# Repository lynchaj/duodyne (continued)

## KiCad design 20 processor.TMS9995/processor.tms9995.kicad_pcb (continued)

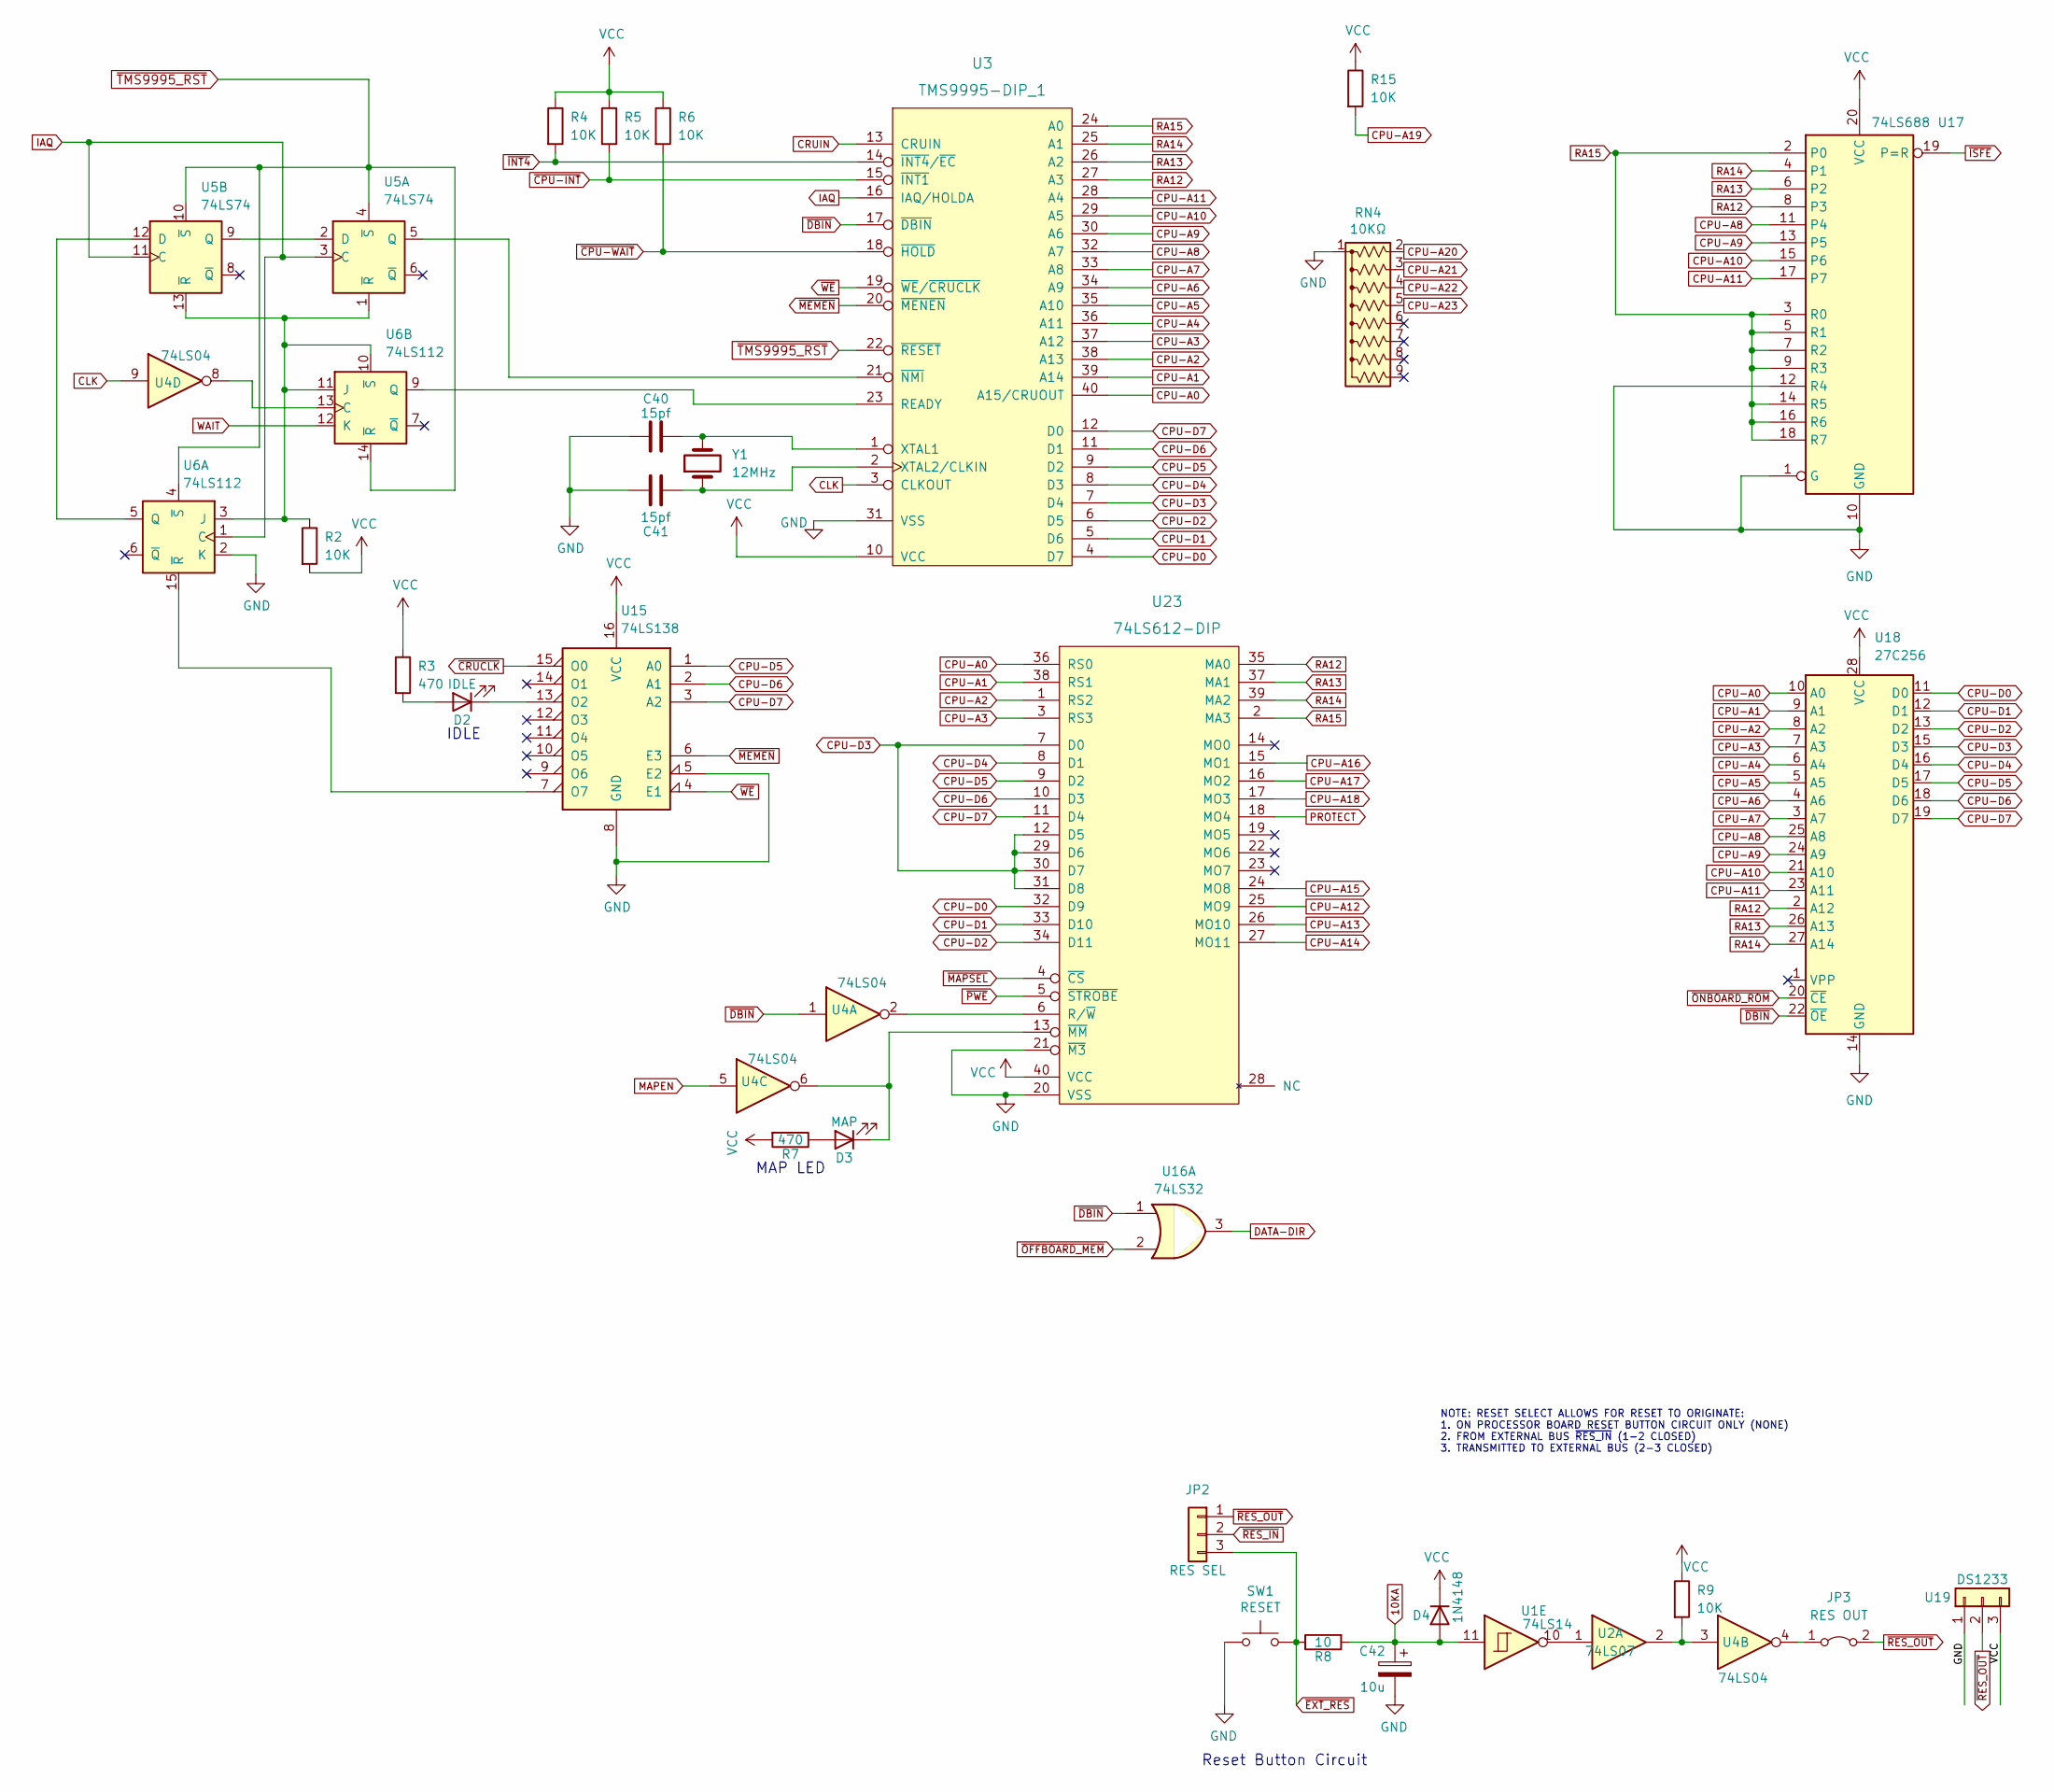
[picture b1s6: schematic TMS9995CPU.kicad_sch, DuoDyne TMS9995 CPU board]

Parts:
C40, C41: 15pf; C_Disc_D5.0mm_W2.5mm_P5.00mm
C42: 10u; CP_Radial_D5.0mm_P2.50mm
D2: IDLE; LED_D3.0mm_Horizontal_O3.81mm_Z2.0mm
D3: MAP; LED_D3.0mm_Horizontal_O3.81mm_Z2.0mm
D4: 1N4148; D_DO-35_SOD27_P7.62mm_Horizontal
JP2: RES SEL; PinHeader_1x03_P2.54mm_Vertical
JP3: RES OUT; SolderJumper-2_P1.3mm_Bridged_Pad1.0x1.5mm
R2, R4, R5, R6, R9, R15: 10K; R_Axial_DIN0207_L6.3mm_D2.5mm_P7.62mm_Horizontal
R3, R7: 470; R_Axial_DIN0207_L6.3mm_D2.5mm_P7.62mm_Horizontal
R8: 10; R_Axial_DIN0207_L6.3mm_D2.5mm_P7.62mm_Horizontal
RN4: 10KΩ; R_Array_SIP9
SW1: RESET; SW_Tactile_SPST_Angled_PTS645Vx58-2LFS
U1: 74LS14; DIP-14_W7.62mm_Socket_LongPads
U2: 74LS07; DIP-14_W7.62mm_Socket_LongPads
U3: TMS9995-DIP_1; DIP-40_W15.24mm_Socket_LongPads
U4: 74LS04; DIP-14_W7.62mm_Socket_LongPads
U5: 74LS74; DIP-14_W7.62mm_Socket_LongPads
U6: 74LS112; DIP-16_W7.62mm_Socket_LongPads
U15: 74LS138; DIP-16_W7.62mm_Socket_LongPads
U16: 74LS32; DIP-14_W7.62mm_Socket_LongPads
U17: 74LS688; DIP-20_W7.62mm_Socket_LongPads
U18: 27C256; DIP-28_W15.24mm_Socket_LongPads
U19: DS1233; TO-92L_HandSolder
U23: 74LS612-DIP; DIP-40_W15.24mm_Socket_LongPads
Y1: 12MHz; Crystal_HC49-U_Vertical

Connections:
10KA: C42.1, D4.2 (A), R8.2, U1.11
CLK: U3.3 (CLKOUT), U4.9; also elsewhere on the board
CPU-A0: U3.40 (A15/CRUOUT), U18.10 (A0), U23.36 (RS0); also elsewhere on the board
CPU-A1: U3.39 (A14), U18.9 (A1), U23.38 (RS1); also elsewhere on the board
CPU-A2: U3.38 (A13), U18.8 (A2), U23.1 (RS2); also elsewhere on the board
CPU-A3: U3.37 (A12), U18.7 (A3), U23.3 (RS3); also elsewhere on the board
CPU-A4: U3.36 (A11), U18.6 (A4); also elsewhere on the board
CPU-A5: U3.35 (A10), U18.5 (A5); also elsewhere on the board
CPU-A6: U3.34 (A9), U18.4 (A6); also elsewhere on the board
CPU-A7: U3.33 (A8), U18.3 (A7); also elsewhere on the board
CPU-A8: U3.32 (A7), U17.11 (P4), U18.25 (A8); also elsewhere on the board
CPU-A9: U3.30 (A6), U17.13 (P5), U18.24 (A9); also elsewhere on the board
CPU-A10: U3.29 (A5), U17.15 (P6), U18.21 (A10); also elsewhere on the board
CPU-A11: U3.28 (A4), U17.17 (P7), U18.23 (A11); also elsewhere on the board
CPU-A12: U23.25 (MO9); also elsewhere on the board
CPU-A13: U23.26 (MO10); also elsewhere on the board
CPU-A14: U23.27 (MO11); also elsewhere on the board
CPU-A15: U23.24 (MO8); also elsewhere on the board
CPU-A16: U23.15 (MO1); also elsewhere on the board
CPU-A17: U23.16 (MO2); also elsewhere on the board
CPU-A18: U23.17 (MO3); also elsewhere on the board
CPU-A19: R15.2; also elsewhere on the board
CPU-A20: RN4.2 (R1); also elsewhere on the board
CPU-A21: RN4.3 (R2); also elsewhere on the board
CPU-A22: RN4.4 (R3); also elsewhere on the board
CPU-A23: RN4.5 (R4); also elsewhere on the board
CPU-D0: U3.4 (D7), U18.11 (D0), U23.32 (D9); also elsewhere on the board
CPU-D1: U3.5 (D6), U18.12 (D1), U23.33 (D10); also elsewhere on the board
CPU-D2: U3.6 (D5), U18.13 (D2), U23.34 (D11); also elsewhere on the board
CPU-D3: U3.7 (D4), U18.15 (D3), U23.7 (D0), U23.12 (D5), U23.29 (D6), U23.30 (D7), U23.31 (D8); also elsewhere on the board
CPU-D4: U3.8 (D3), U18.16 (D4), U23.8 (D1); also elsewhere on the board
CPU-D5: U3.9 (D2), U15.1 (A0), U18.17 (D5), U23.9 (D2); also elsewhere on the board
CPU-D6: U3.11 (D1), U15.2 (A1), U18.18 (D6), U23.10 (D3); also elsewhere on the board
CPU-D7: U3.12 (D0), U15.3 (A2), U18.19 (D7), U23.11 (D4); also elsewhere on the board
CRUIN: U3.13 (CRUIN); also elsewhere on the board
DATA-DIR: U16.3; also elsewhere on the board
GND: C40.1, C41.1, C42.2, RN4.1 (common), SW1.2, U3.31 (VSS), U6.2 (K), U15.5 (E2), U15.8 (GND), U17.1 (G), U17.10 (GND), U17.12 (R4), U18.14 (GND), U19.1, U23.20 (VSS), U23.21 (~M3); also elsewhere on the board
IAQ: U3.16 (IAQ/HOLDA), U5.3 (C), U5.11 (C), U6.1 (C)
MAPEN: U4.5; also elsewhere on the board
unnamed: C40.2, U3.1 (XTAL1), Y1.2
unnamed: C41.2, U3.2 (XTAL2/CLKIN), Y1.1
unnamed: D2.1 (K), U15.13 (O2)
unnamed: D2.2 (A), R3.2
unnamed: D3.1 (K), U4.6, U23.13 (~MM)
unnamed: D3.2 (A), R7.1
unnamed: JP3.1 (A), U4.4
unnamed: R2.1, U5.1 (~R), U5.13 (~R), U6.3 (J), U6.10 (~S), U6.11 (J)
unnamed: R9.2, U2.2, U4.3
unnamed: U1.10, U2.1
unnamed: U4.2, U23.6 (R/~W)
unnamed: U4.8, U6.13 (C)
unnamed: U5.2 (D), U5.9 (Q)
unnamed: U3.21 (~NMI), U5.5 (Q)
unnamed: U5.12 (D), U6.5 (Q)
unnamed: U3.23 (READY), U6.9 (Q)
unnamed: U6.15 (~R), U15.7 (O7)
PROTECT: U23.18 (MO4); also elsewhere on the board
RA12: U3.27 (A3), U17.8 (P3), U18.2 (A12), U23.35 (MA0)
RA13: U3.26 (A2), U17.6 (P2), U18.26 (A13), U23.37 (MA1)
RA14: U3.25 (A1), U17.4 (P1), U18.27 (A14), U23.39 (MA2)
RA15: U3.24 (A0), U17.2 (P0), U17.3 (R0), U17.5 (R1), U17.7 (R2), U17.9 (R3), U17.14 (R5), U17.16 (R6), U17.18 (R7), U23.2 (MA3); also elsewhere on the board
VCC: D4.1 (K), R2.2, R3.1, R4.1, R5.1, R6.1, R7.2, R9.1, R15.1, U3.10 (VCC), U15.16 (VCC), U17.20 (VCC), U18.28 (VCC), U19.3, U23.40 (VCC); also elsewhere on the board
WAIT: U6.12 (K); also elsewhere on the board
~CPU-INT: R5.2, U3.15 (~INT1); also elsewhere on the board
~CPU-WAIT: R6.2, U3.18 (~HOLD); also elsewhere on the board
~CRUCLK: U15.15 (O0); also elsewhere on the board
~DBIN: U3.17 (~DBIN), U4.1, U16.1, U18.22 (~OE); also elsewhere on the board
~EXT_RES: JP2.3, R8.1, SW1.1
~INT4: R4.2, U3.14 (~INT4/~EC); also elsewhere on the board
~ISFE: U17.19 (P=R); also elsewhere on the board
~MAPSEL: U23.4 (~CS); also elsewhere on the board
~MEMEN: U3.20 (~MENEN), U15.6 (E3); also elsewhere on the board
~OFFBOARD_MEM: U16.2; also elsewhere on the board
~ONBOARD_ROM: U18.20 (~CE); also elsewhere on the board
~PWE: U23.5 (~STROBE); also elsewhere on the board
~RES_IN: JP2.2; also elsewhere on the board
~RES_OUT: JP2.1, JP3.2 (B), U19.2; also elsewhere on the board
~TMS9995_RST: U3.22 (~RESET), U5.4 (~S), U5.10 (~S), U6.4 (~S), U6.14 (~R); also elsewhere on the board
~WE: U3.19 (~WE/~CRUCLK), U15.4 (E1); also elsewhere on the board

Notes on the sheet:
Reset Button Circuit
MAP LED
IDLE
NOTE: RESET SELECT ALLOWS FOR RESET TO ORIGINATE: 1. ON PROCESSOR BOARD RESET BUTTON CIRCUIT ONLY (NONE) 2. FROM EXTERNAL BUS ~{RES_IN} (1-2 CLOSED) 3. TRANSMITTED TO EXTERNAL BUS (2-3 CLOSED)

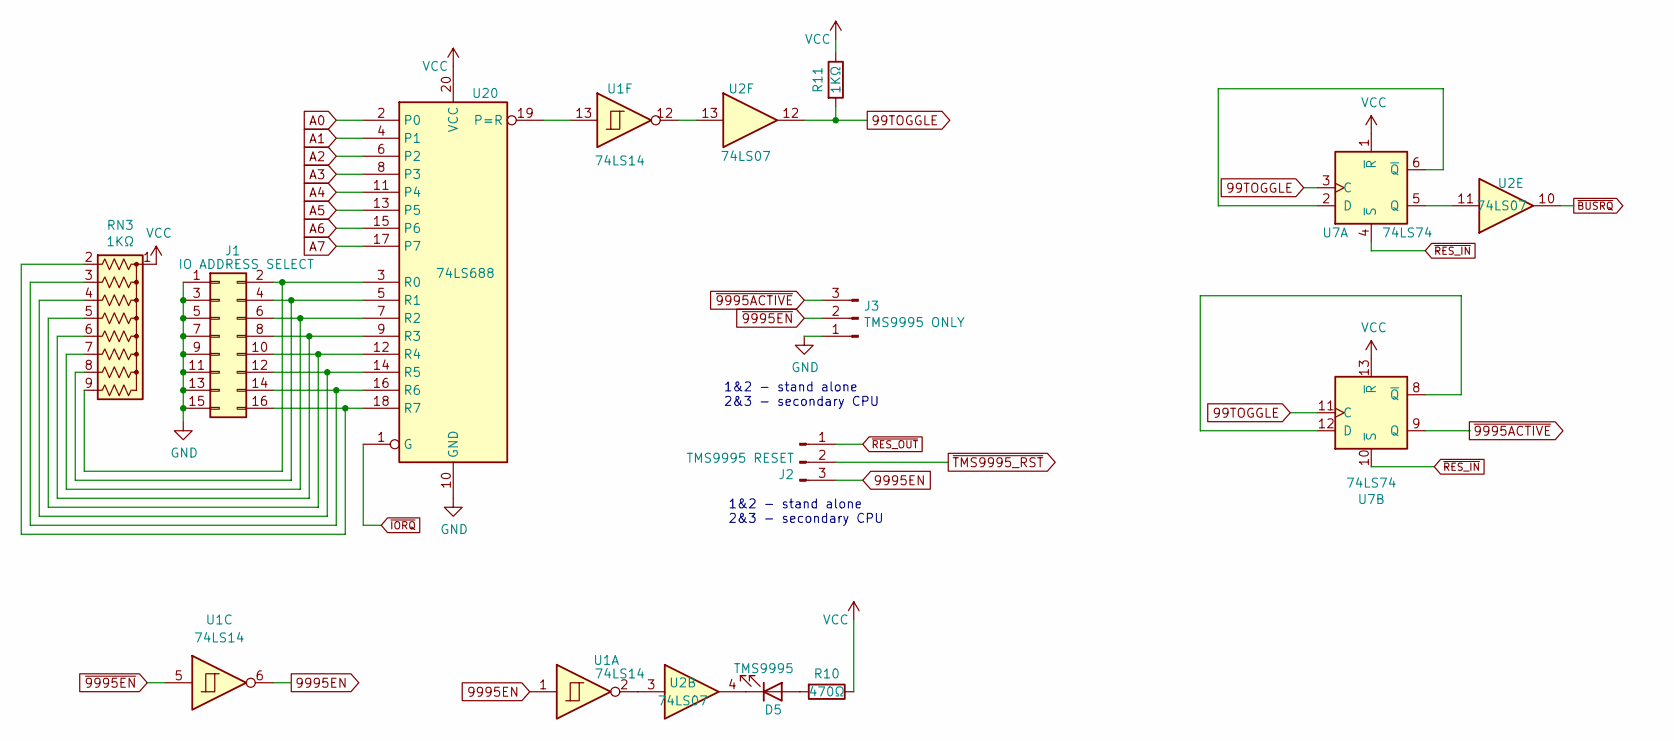
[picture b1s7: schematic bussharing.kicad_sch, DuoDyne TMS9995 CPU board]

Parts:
D5: TMS9995; LED_D3.0mm_Horizontal_O3.81mm_Z2.0mm
J1: IO ADDRESS SELECT; PinHeader_2x08_P2.54mm_Vertical
J2: TMS9995 RESET; PinHeader_1x03_P2.54mm_Horizontal
J3: TMS9995 ONLY; PinHeader_1x03_P2.54mm_Horizontal
R10: 470Ω; R_Axial_DIN0207_L6.3mm_D2.5mm_P7.62mm_Horizontal
R11: 1KΩ; R_Axial_DIN0207_L6.3mm_D2.5mm_P7.62mm_Horizontal
RN3: 1KΩ; R_Array_SIP9
U1: 74LS14; DIP-14_W7.62mm_Socket_LongPads
U2: 74LS07; DIP-14_W7.62mm_Socket_LongPads
U7: 74LS74; DIP-14_W7.62mm_Socket_LongPads
U20: 74LS688; DIP-20_W7.62mm_Socket_LongPads

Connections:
99TOGGLE: R11.2, U2.12, U7.3 (C), U7.11 (C)
9995EN: J2.3, U1.1, U1.6
A0: U20.2 (P0); also elsewhere on the board
A1: U20.4 (P1); also elsewhere on the board
A2: U20.6 (P2); also elsewhere on the board
A3: U20.8 (P3); also elsewhere on the board
A4: U20.11 (P4); also elsewhere on the board
A5: U20.13 (P5); also elsewhere on the board
A6: U20.15 (P6); also elsewhere on the board
A7: U20.17 (P7); also elsewhere on the board
GND: J1.1, J1.3, J1.5, J1.7, J1.9, J1.11, J1.13, J1.15, J3.1, U20.10 (GND); also elsewhere on the board
unnamed: D5.1 (K), U2.4
unnamed: D5.2 (A), R10.2
unnamed: J1.2, RN3.9 (R8), U20.3 (R0)
unnamed: J1.4, RN3.8 (R7), U20.5 (R1)
unnamed: J1.6, RN3.7 (R6), U20.7 (R2)
unnamed: J1.8, RN3.6 (R5), U20.9 (R3)
unnamed: J1.10, RN3.5 (R4), U20.12 (R4)
unnamed: J1.12, RN3.4 (R3), U20.14 (R5)
unnamed: J1.14, RN3.3 (R2), U20.16 (R6)
unnamed: J1.16, RN3.2 (R1), U20.18 (R7)
unnamed: U1.12, U2.13
unnamed: U1.13, U20.19 (P=R)
unnamed: U1.2, U2.3
unnamed: U2.11, U7.5 (Q)
unnamed: U7.2 (D), U7.6 (~Q)
unnamed: U7.8 (~Q), U7.12 (D)
VCC: R10.1, R11.1, RN3.1 (common), U7.1 (~R), U7.13 (~R), U20.20 (VCC); also elsewhere on the board
~9995ACTIVE: J3.3, U7.9 (Q)
~9995EN: J3.2, U1.5; also elsewhere on the board
~BUSRQ: U2.10; also elsewhere on the board
~IORQ: U20.1 (G); also elsewhere on the board
~RES_IN: U7.4 (~S), U7.10 (~S); also elsewhere on the board
~RES_OUT: J2.1; also elsewhere on the board
~TMS9995_RST: J2.2; also elsewhere on the board

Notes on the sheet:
1&2 - stand alone 2&3 - secondary CPU

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
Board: 2 copper layers, 94 parts (0 on the bottom side), 184 nets, no tracks yet.

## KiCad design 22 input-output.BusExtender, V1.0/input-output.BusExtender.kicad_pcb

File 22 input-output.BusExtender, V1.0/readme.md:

This board extends the duodyne bus to the top of the other boards to aid in debugging and new board development

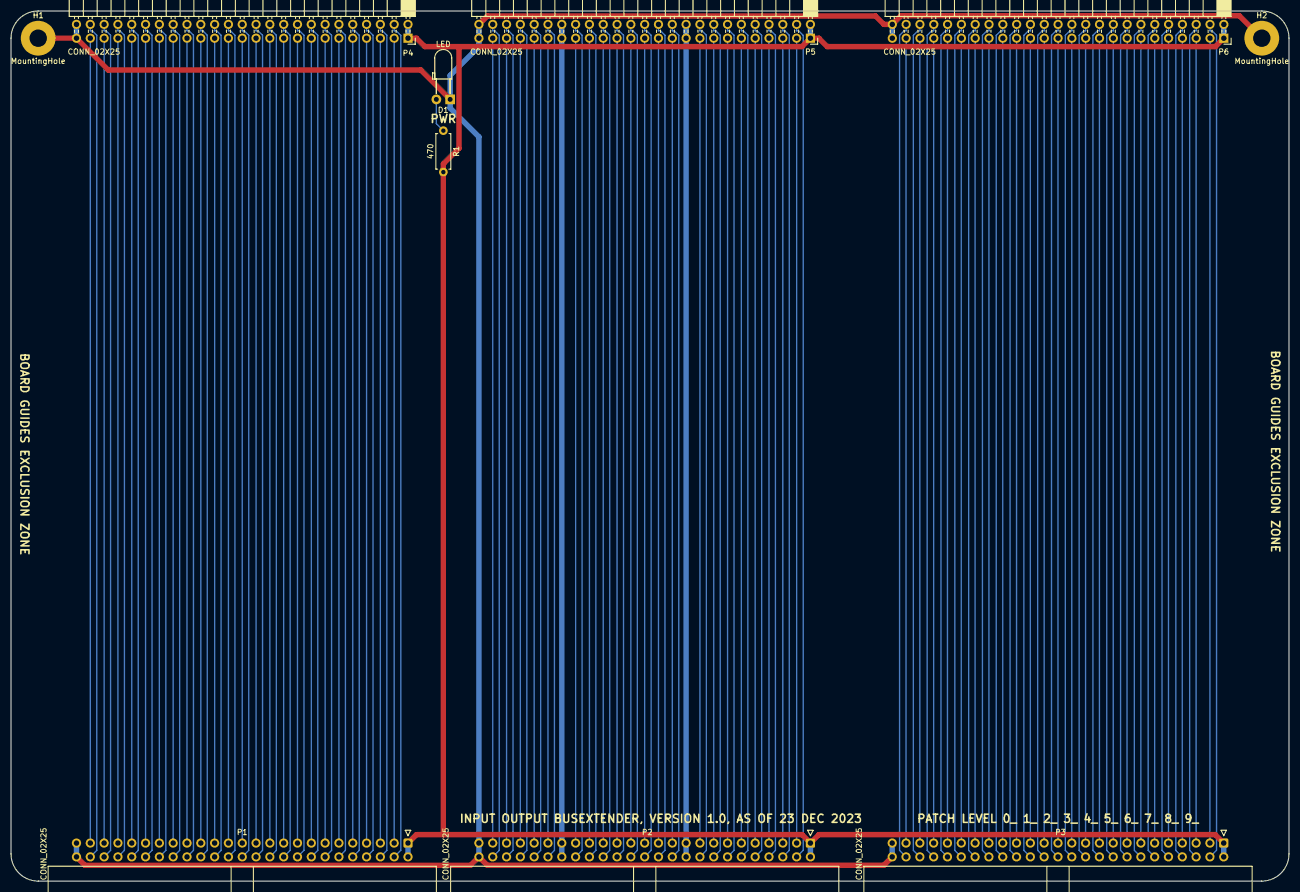
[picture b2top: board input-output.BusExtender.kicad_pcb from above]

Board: 2 copper layers, 235.0 x 160.0 mm, 10 parts (0 on the bottom side), 139 nets.

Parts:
D1: LED; LED_D3.0mm_Horizontal_O3.81mm_Z2.0mm
H1, H2: MountingHole; MountingHole_3.2mm_M3_Pad
P1, P2, P3: CONN_02X25; IDC-Header_2x25_P2.54mm_Horizontal
P4, P5, P6: CONN_02X25; PinSocket_2x25_P2.54mm_Horizontal
R1: 470; R_Axial_DIN0207_L6.3mm_D2.5mm_P7.62mm_Horizontal

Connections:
+12V: P2.19, P2.20, P5.19, P5.20
-12V: P2.37, P2.38, P5.37, P5.38
/bus/A16: P2.36, P5.36
/bus/A17: P2.34, P5.34
/bus/A18: P2.32, P5.32
/bus/A19: P2.30, P5.30
/bus/A20: P2.28, P5.28
/bus/A21: P2.26, P5.26
/bus/A22: P2.24, P5.24
/bus/A23: P2.22, P5.22
/bus/A24: P2.18, P5.18
/bus/A25: P2.16, P5.16
/bus/A26: P2.14, P5.14
/bus/A27: P2.12, P5.12
/bus/A28: P2.10, P5.10
/bus/A29: P2.8, P5.8
/bus/A30: P2.6, P5.6
/bus/A31: P2.4, P5.4
/bus/AUXCLK0: P2.48, P5.48
/bus/AUXCLK1: P2.47, P5.47
/bus/AUXCLK2: P3.48, P6.48
/bus/AUXCLK3: P3.46, P6.46
/bus/CLK: P1.15, P4.15
/bus/CRUCLK: P1.14, P4.14
/bus/CRUIN: P1.18, P4.18
/bus/CRUOUT: P1.16, P4.16
/bus/D8: P3.17, P6.17
/bus/D9: P3.15, P6.15
/bus/D10: P3.13, P6.13
/bus/D11: P3.11, P6.11
/bus/D12: P3.9, P6.9
/bus/D13: P3.7, P6.7
/bus/D14: P3.5, P6.5
/bus/D15: P3.3, P6.3
/bus/D16: P3.34, P6.34
/bus/D17: P3.32, P6.32
/bus/D18: P3.30, P6.30
/bus/D19: P3.28, P6.28
/bus/D20: P3.26, P6.26
/bus/D21: P3.24, P6.24
/bus/D22: P3.22, P6.22
/bus/D23: P3.20, P6.20
/bus/D24: P3.18, P6.18
/bus/D25: P3.16, P6.16
/bus/D26: P3.14, P6.14
/bus/D27: P3.12, P6.12
/bus/D28: P3.10, P6.10
/bus/D29: P3.8, P6.8
/bus/D30: P3.6, P6.6
/bus/D31: P3.4, P6.4
/bus/E: P1.4, P4.4
/bus/IC0: P2.45, P5.45
/bus/IC1: P2.43, P5.43
/bus/IC2: P2.41, P5.41
/bus/IC3: P2.39, P5.39
/bus/IPL0: P3.47, P6.47
/bus/IPL1: P3.45, P6.45
/bus/IPL2: P3.43, P6.43
/bus/LDS: P3.38, P6.38
/bus/PHI: P1.8, P4.8
/bus/S0: P3.44, P6.44
/bus/S1: P3.42, P6.42
/bus/S2: P3.40, P6.40
/bus/ST: P1.6, P4.6
/bus/UDS: P3.36, P6.36
/bus/USER0: P1.38, P4.38
/bus/USER1: P1.36, P4.36
/bus/USER2: P1.34, P4.34
/bus/USER3: P1.32, P4.32
/bus/USER4: P1.30, P4.30
/bus/USER5: P1.28, P4.28
/bus/USER6: P1.26, P4.26
/bus/USER7: P1.24, P4.24
/bus/USER8: P1.22, P4.22
/bus/~BHE: P3.41, P6.41
/bus/~BUSERR: P3.35, P6.35
/bus/~DREQ0: P2.46, P5.46
/bus/~DREQ1: P2.42, P5.42
/bus/~EIRQ0: P1.45, P4.45
/bus/~EIRQ1: P1.43, P4.43
/bus/~EIRQ2: P1.41, P4.41
/bus/~EIRQ3: P1.39, P4.39
/bus/~EIRQ4: P1.37, P4.37
/bus/~EIRQ5: P1.35, P4.35
/bus/~EIRQ6: P1.33, P4.33
/bus/~EIRQ7: P1.31, P4.31
/bus/~INT1: P1.12, P4.12
/bus/~INT2: P1.10, P4.10
/bus/~TEND0: P2.44, P5.44
/bus/~TEND1: P2.40, P5.40
/bus/~VMA: P3.39, P6.39
/bus/~VPA: P3.37, P6.37
/bus/~WAIT: P1.25, P4.25
A0: P2.35, P5.35
A1: P2.33, P5.33
A2: P2.31, P5.31
A3: P2.29, P5.29
A4: P2.27, P5.27
A5: P2.25, P5.25
A6: P2.23, P5.23
A7: P2.21, P5.21
A8: P2.17, P5.17
A9: P2.15, P5.15
A10: P2.13, P5.13
A11: P2.11, P5.11
A12: P2.9, P5.9
A13: P2.7, P5.7
A14: P2.5, P5.5
A15: P2.3, P5.3
D0: P3.33, P6.33
D1: P3.31, P6.31
D2: P3.29, P6.29
D3: P3.27, P6.27
D4: P3.25, P6.25
D5: P3.23, P6.23
D6: P3.21, P6.21
D7: P3.19, P6.19
GND: D1.1 (K), H1.1, H2.1, P1.49, P1.50, P2.49, P2.50, P3.49, P3.50, P4.49, P4.50, P5.49, P5.50, P6.49, P6.50
I2C_SCL: P1.47, P4.47
I2C_SDA: P1.48, P4.48
unnamed: D1.2 (A), R1.1
VCC: P1.1, P1.2, P2.1, P2.2, P3.1, P3.2, P4.1, P4.2, P5.1, P5.2, P6.1, P6.2, R1.2
~BAI: P1.40, P4.40
~BAO: P1.42, P4.42
~BUSACK: P1.13, P4.13
~BUSRQ: P1.23, P4.23
~HALT: P1.27, P4.27
~IEI: P1.44, P4.44
~IEO: P1.46, P4.46
~INT0: P1.17, P4.17
~IORQ: P1.7, P4.7
~M1: P1.11, P4.11
~MREQ: P1.9, P4.9
~NMI: P1.19, P4.19
~RD: P1.3, P4.3
~RES_IN: P1.20, P4.20
~RES_OUT: P1.21, P4.21
~RFSH: P1.29, P4.29
~WR: P1.5, P4.5

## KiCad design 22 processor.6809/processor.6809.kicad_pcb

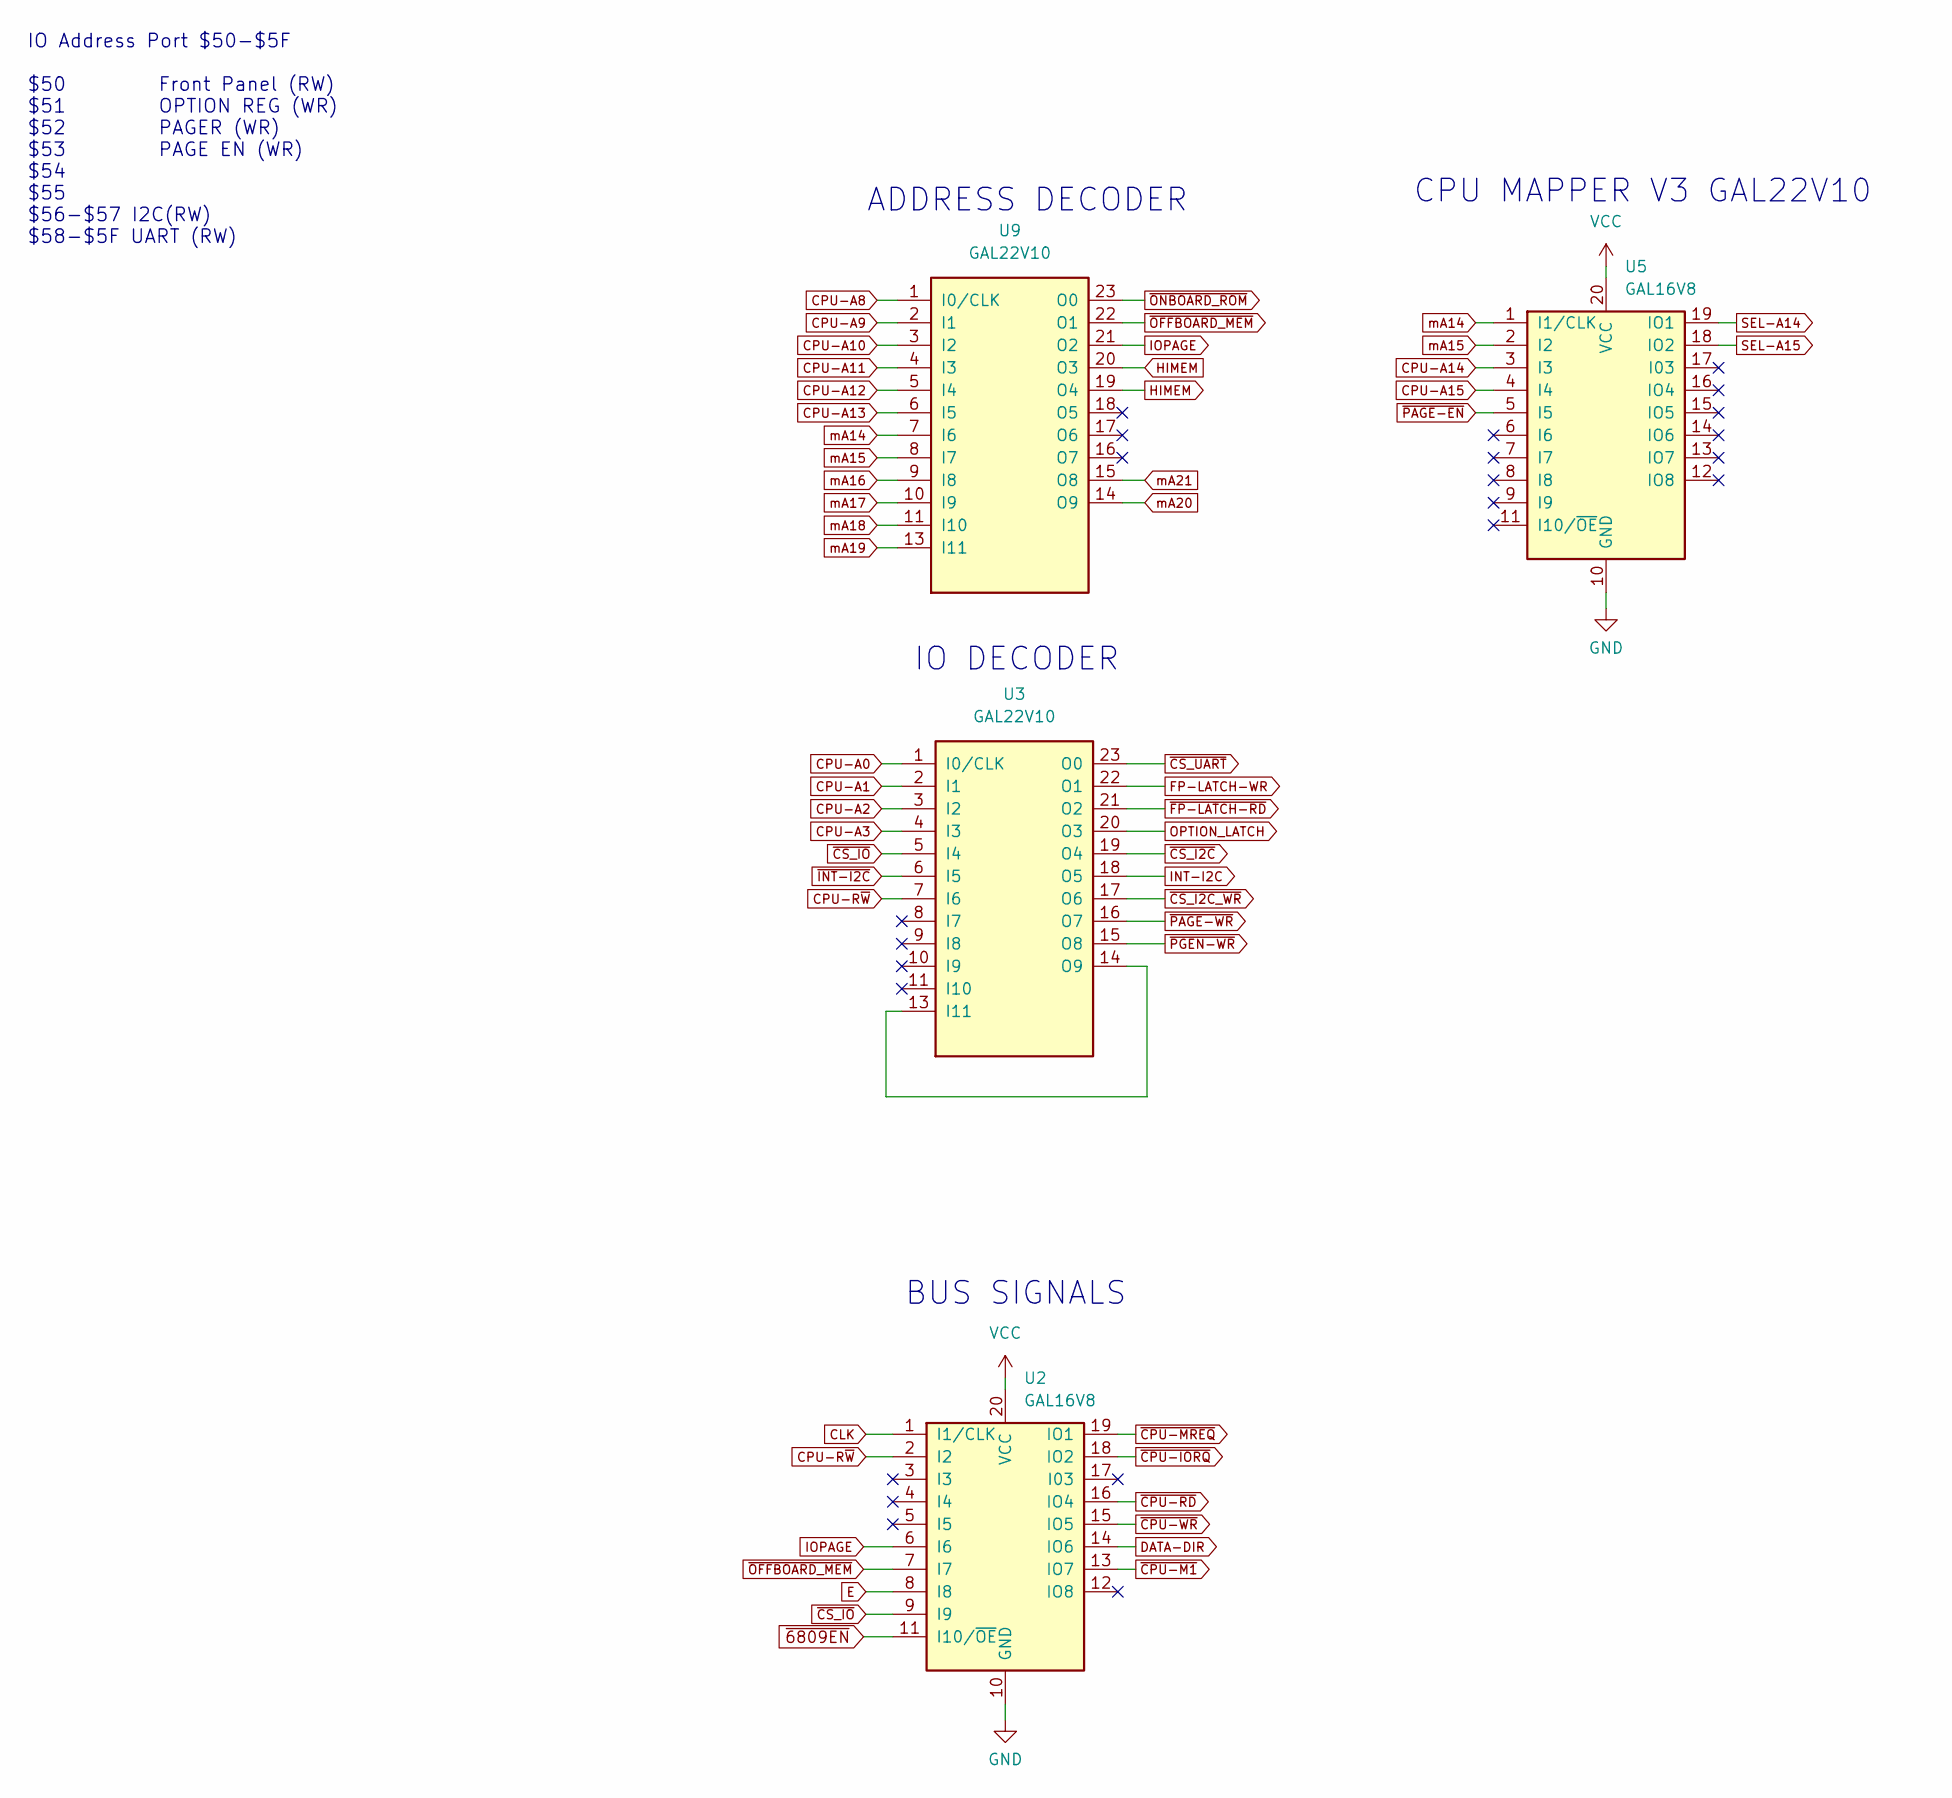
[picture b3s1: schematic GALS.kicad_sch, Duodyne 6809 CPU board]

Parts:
U2, U5: GAL16V8; DIP-20_W7.62mm_Socket_LongPads
U3, U9: GAL22V10; DIP-24_W7.62mm_Socket_LongPads

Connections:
CLK: U2.1 (I1/CLK); also elsewhere on the board
CPU-A0: U3.1 (I0/CLK); also elsewhere on the board
CPU-A1: U3.2 (I1); also elsewhere on the board
CPU-A2: U3.3 (I2); also elsewhere on the board
CPU-A3: U3.4 (I3); also elsewhere on the board
CPU-A8: U9.1 (I0/CLK); also elsewhere on the board
CPU-A9: U9.2 (I1); also elsewhere on the board
CPU-A10: U9.3 (I2); also elsewhere on the board
CPU-A11: U9.4 (I3); also elsewhere on the board
CPU-A12: U9.5 (I4); also elsewhere on the board
CPU-A13: U9.6 (I5); also elsewhere on the board
CPU-A14: U5.3 (I3); also elsewhere on the board
CPU-A15: U5.4 (I4); also elsewhere on the board
CPU-R~W: U2.2 (I2), U3.7 (I6); also elsewhere on the board
DATA-DIR: U2.14 (IO6); also elsewhere on the board
E: U2.8 (I8); also elsewhere on the board
FP-LATCH-WR: U3.22 (O1); also elsewhere on the board
GND: U2.10 (GND), U3.12 (GND), U5.10 (GND), U9.12 (GND); also elsewhere on the board
HIMEM: U9.19 (O4), U9.20 (O3)
INT-I2C: U3.18 (O5); also elsewhere on the board
IOPAGE: U2.6 (I6), U9.21 (O2)
unnamed: U3.13 (I11), U3.14 (O9)
OPTION_LATCH: U3.20 (O3); also elsewhere on the board
SEL-A14: U5.19 (IO1); also elsewhere on the board
SEL-A15: U5.18 (IO2); also elsewhere on the board
VCC: U2.20 (VCC), U3.24 (VCC), U5.20 (VCC), U9.24 (VCC); also elsewhere on the board
mA14: U5.1 (I1/CLK), U9.7 (I6); also elsewhere on the board
mA15: U5.2 (I2), U9.8 (I7); also elsewhere on the board
mA16: U9.9 (I8); also elsewhere on the board
mA17: U9.10 (I9); also elsewhere on the board
mA18: U9.11 (I10); also elsewhere on the board
mA19: U9.13 (I11); also elsewhere on the board
mA20: U9.14 (O9); also elsewhere on the board
mA21: U9.15 (O8); also elsewhere on the board
~6809EN: U2.11 (I10/~OE); also elsewhere on the board
~CPU-IORQ: U2.18 (IO2); also elsewhere on the board
~CPU-M1: U2.13 (IO7); also elsewhere on the board
~CPU-MREQ: U2.19 (IO1); also elsewhere on the board
~CPU-RD: U2.16 (IO4); also elsewhere on the board
~CPU-WR: U2.15 (IO5); also elsewhere on the board
~CS_I2C_WR: U3.17 (O6); also elsewhere on the board
~CS_I2C: U3.19 (O4); also elsewhere on the board
~CS_IO: U2.9 (I9), U3.5 (I4); also elsewhere on the board
~CS_UART: U3.23 (O0); also elsewhere on the board
~FP-LATCH-RD: U3.21 (O2); also elsewhere on the board
~INT-I2C: U3.6 (I5); also elsewhere on the board
~OFFBOARD_MEM: U2.7 (I7), U9.22 (O1)
~ONBOARD_ROM: U9.23 (O0); also elsewhere on the board
~PAGE-EN: U5.5 (I5); also elsewhere on the board
~PAGE-WR: U3.16 (O7); also elsewhere on the board
~PGEN-WR: U3.15 (O8); also elsewhere on the board

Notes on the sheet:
CPU MAPPER V3 GAL22V10
ADDRESS DECODER
IO DECODER
IO Address Port $50-$5F $50 Front Panel (RW) $51 OPTION REG (WR) $52 PAGER (WR) $53 PAGE EN (WR) $54 $55 $56-$57 I2C(RW) $58-$5F UART (RW)
BUS SIGNALS
